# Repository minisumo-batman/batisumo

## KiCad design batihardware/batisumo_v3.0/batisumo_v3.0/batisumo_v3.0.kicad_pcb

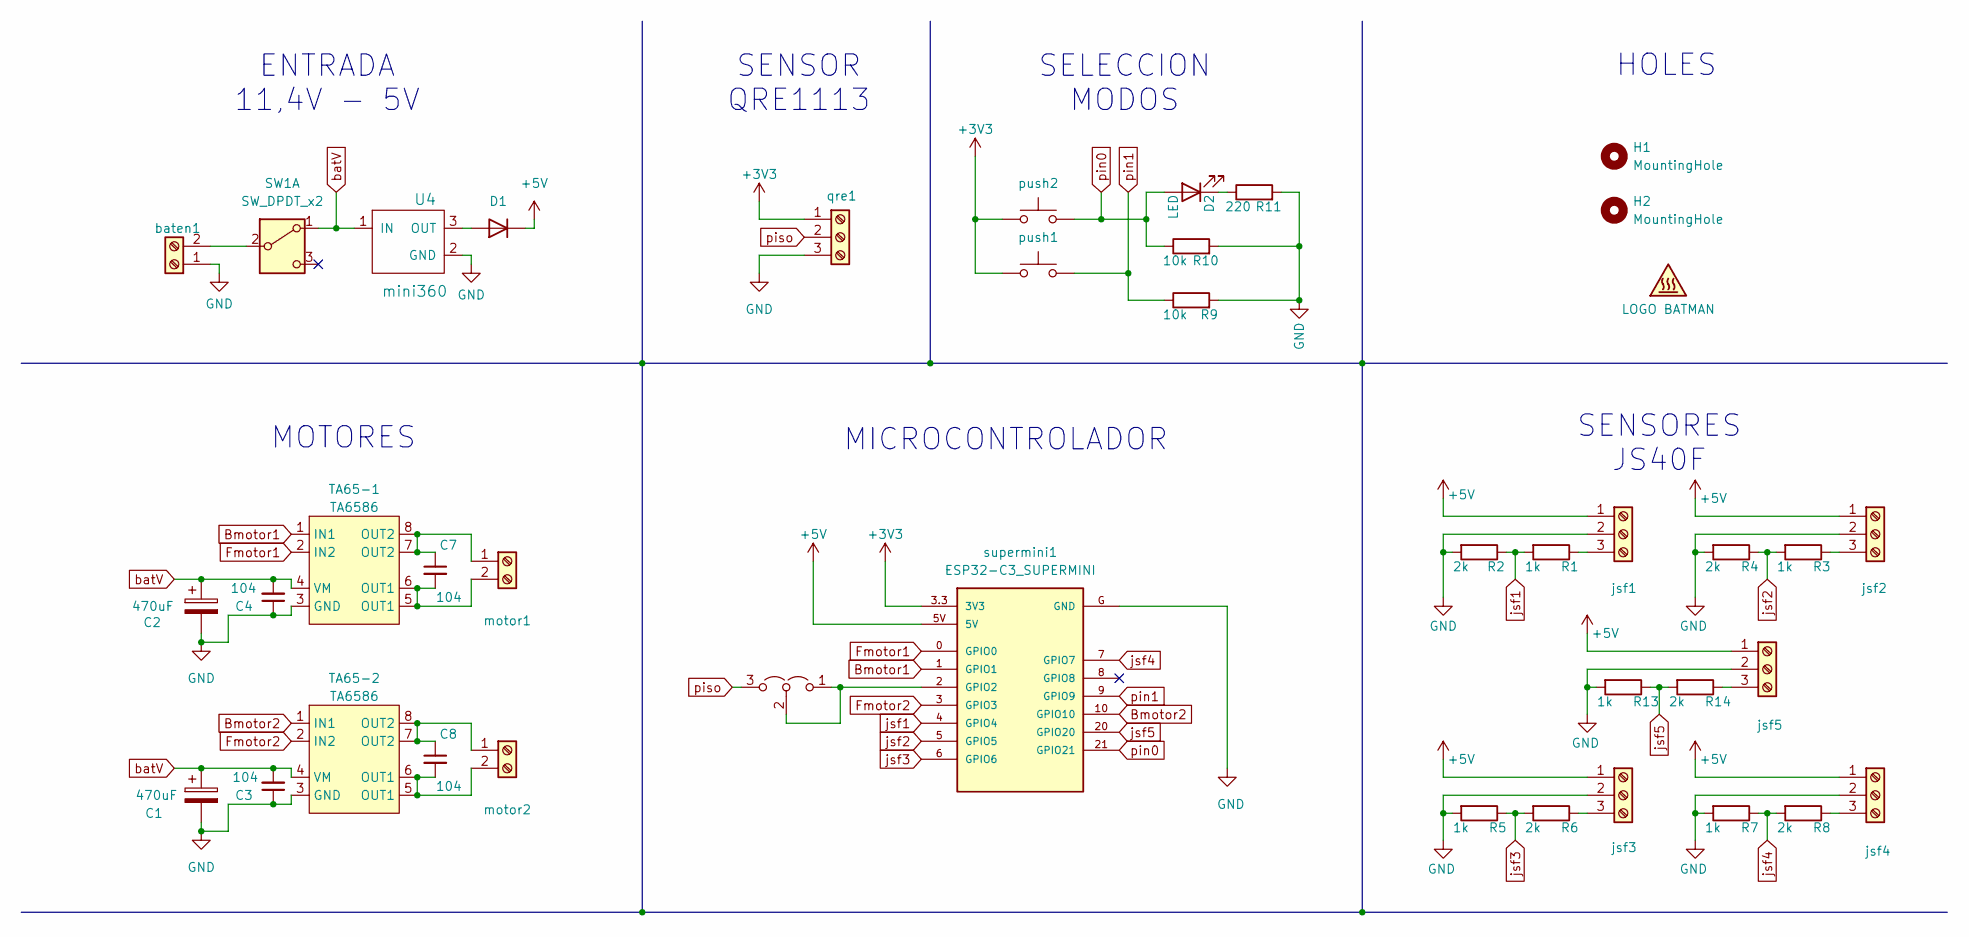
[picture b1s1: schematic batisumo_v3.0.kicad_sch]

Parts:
C1, C2: 470uF; CP_EIA-7343-43_Kemet-X
C3, C4, C7, C8: 104; C_0805_2012Metric
D1: D_2010_5025Metric_Pad1.52x2.65mm_HandSolder
D2: LED; LED_0805_2012Metric
H1, H2: MountingHole; MountingHole_3.2mm_M3
JP2: PinSocket_1x03_P2.54mm_Vertical
R1, R3, R5, R7, R13: 1k; R_0805_2012Metric
R2, R4, R6, R8, R14: 2k; R_0805_2012Metric
R9, R10: 10k; R_0805_2012Metric
R11: 220; R_0805_2012Metric
SW1: SW_DPDT_x2; SW_Slide-03_P2.54_L9_W4_H7
TA65-1, TA65-2: TA6586; DIP-8_W7.62mm
U4: mini360; Mini360_step-down
baten1: AMASS_XT30U-M_1x02_P5.0mm_Vertical
jsf1, jsf2, jsf3, jsf4, jsf5: JST_PH_B3B-PH-K_1x03_P2.00mm_Vertical
motor1, motor2: PinHeader_1x02_P2.54mm_Vertical
push1, push2: SW_Tactile_SPST_NO_Straight_CK_PTS636Sx25SMTRLFS
qre1: JST_PH_B3B-PH-K_1x03_P2.00mm_Vertical
supermini1: ESP32-C3_SUPERMINI; MODULE_ESP32-C3_SUPERMINI

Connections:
+3V3: push1.1, push2.1, qre1.1, supermini1.3.3 (3V3)
+5V: D1.1 (K), jsf1.1, jsf2.1, jsf3.1, jsf4.1, jsf5.1, supermini1.5V
Bmotor1: TA65-1.1 (IN1), supermini1.1 (GPIO1)
Bmotor2: TA65-2.1 (IN1), supermini1.10 (GPIO10)
Fmotor1: TA65-1.2 (IN2), supermini1.0 (GPIO0)
Fmotor2: TA65-2.2 (IN2), supermini1.3 (GPIO3)
GND: C1.2, C2.2, C3.1, C4.1, R2.2, R4.2, R5.2, R7.2, R9.2, R10.2, R11.2, R13.2, TA65-1.3 (GND), TA65-2.3 (GND), U4.2 (GND), baten1.1, jsf1.2, jsf2.2, jsf3.2, jsf4.2, jsf5.2, qre1.3, supermini1.G (GND)
unnamed: D1.2 (A), U4.3 (OUT)
unnamed: D2.1 (K), R11.1
unnamed: JP2.1 (A), JP2.2 (C), supermini1.2 (GPIO2)
unnamed: SW1.2 (B), baten1.2
unnamed: R1.1, jsf1.3
unnamed: R3.1, jsf2.3
unnamed: R6.1, jsf3.3
unnamed: R8.1, jsf4.3
unnamed: R14.1, jsf5.3
unnamed: C7.1, TA65-1.7 (OUT2), TA65-1.8 (OUT2), motor1.1
unnamed: C7.2, TA65-1.5 (OUT1), TA65-1.6 (OUT1), motor1.2
unnamed: C8.1, TA65-2.7 (OUT2), TA65-2.8 (OUT2), motor2.1
unnamed: C8.2, TA65-2.5 (OUT1), TA65-2.6 (OUT1), motor2.2
batV: C1.1, C2.1, C3.2, C4.2, SW1.1 (A), TA65-1.4 (VM), TA65-2.4 (VM), U4.1 (IN)
jsf1: R1.2, R2.1, supermini1.4 (GPIO4)
jsf2: R3.2, R4.1, supermini1.5 (GPIO5)
jsf3: R5.1, R6.2, supermini1.6 (GPIO6)
jsf4: R7.1, R8.2, supermini1.7 (GPIO7)
jsf5: R13.1, R14.2, supermini1.20 (GPIO20)
pin0: D2.2 (A), R10.1, push2.2, supermini1.21 (GPIO21)
pin1: R9.1, push1.2, supermini1.9 (GPIO9)
piso: JP2.3 (B), qre1.2

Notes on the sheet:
MOTORES
ENTRADA 11,4V - 5V
SENSOR QRE1113
SENSORES JS40F
HOLES
MICROCONTROLADOR
SELECCION MODOS

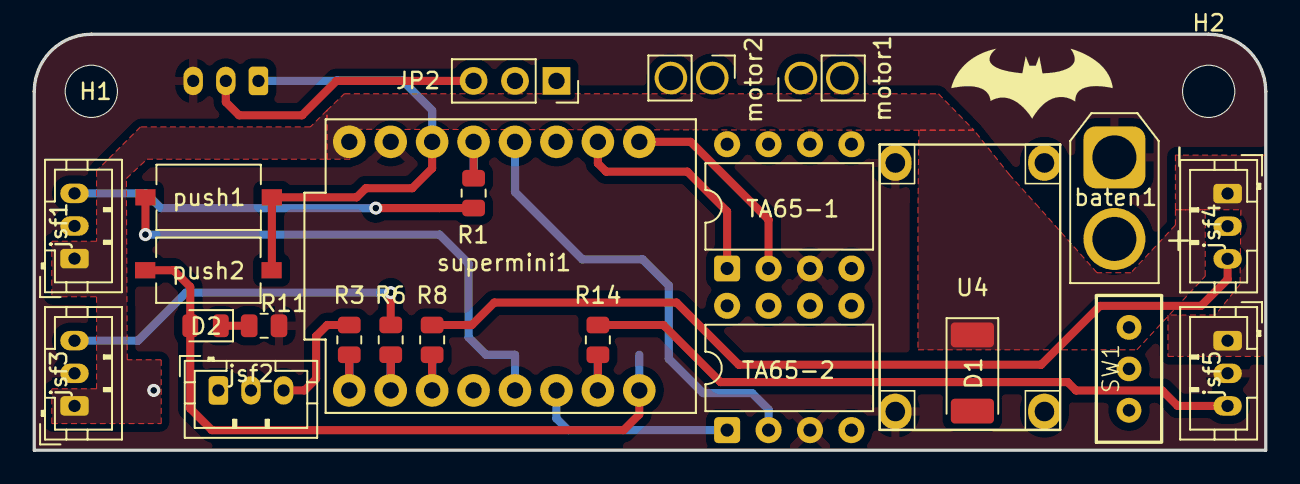
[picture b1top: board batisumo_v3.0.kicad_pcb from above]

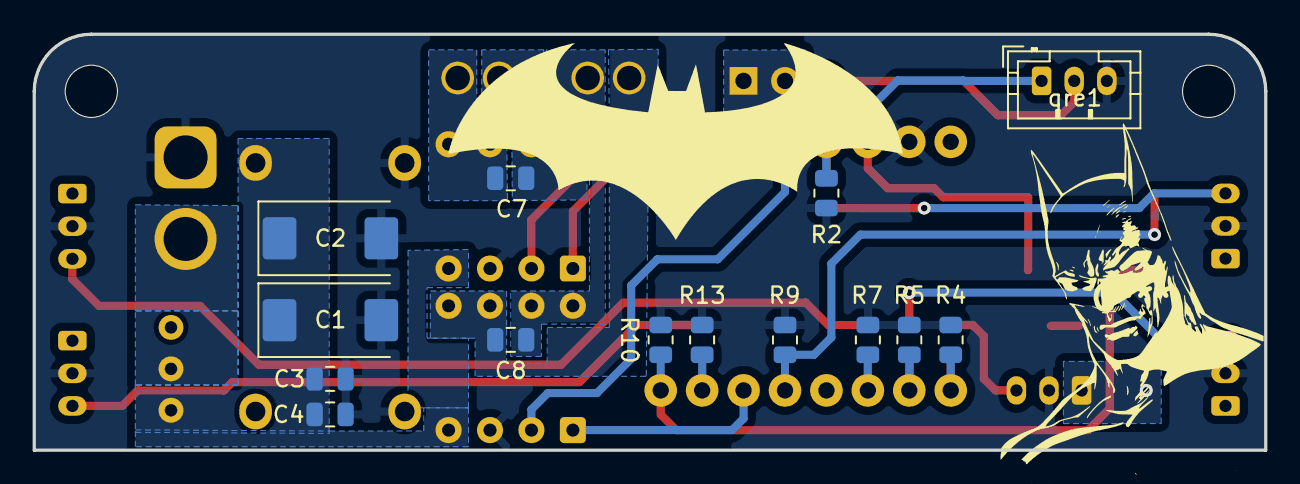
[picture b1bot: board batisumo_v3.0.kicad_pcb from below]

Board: 4 copper layers, 75.5 x 25.5 mm, 40 parts (14 on the bottom side), 29 nets.

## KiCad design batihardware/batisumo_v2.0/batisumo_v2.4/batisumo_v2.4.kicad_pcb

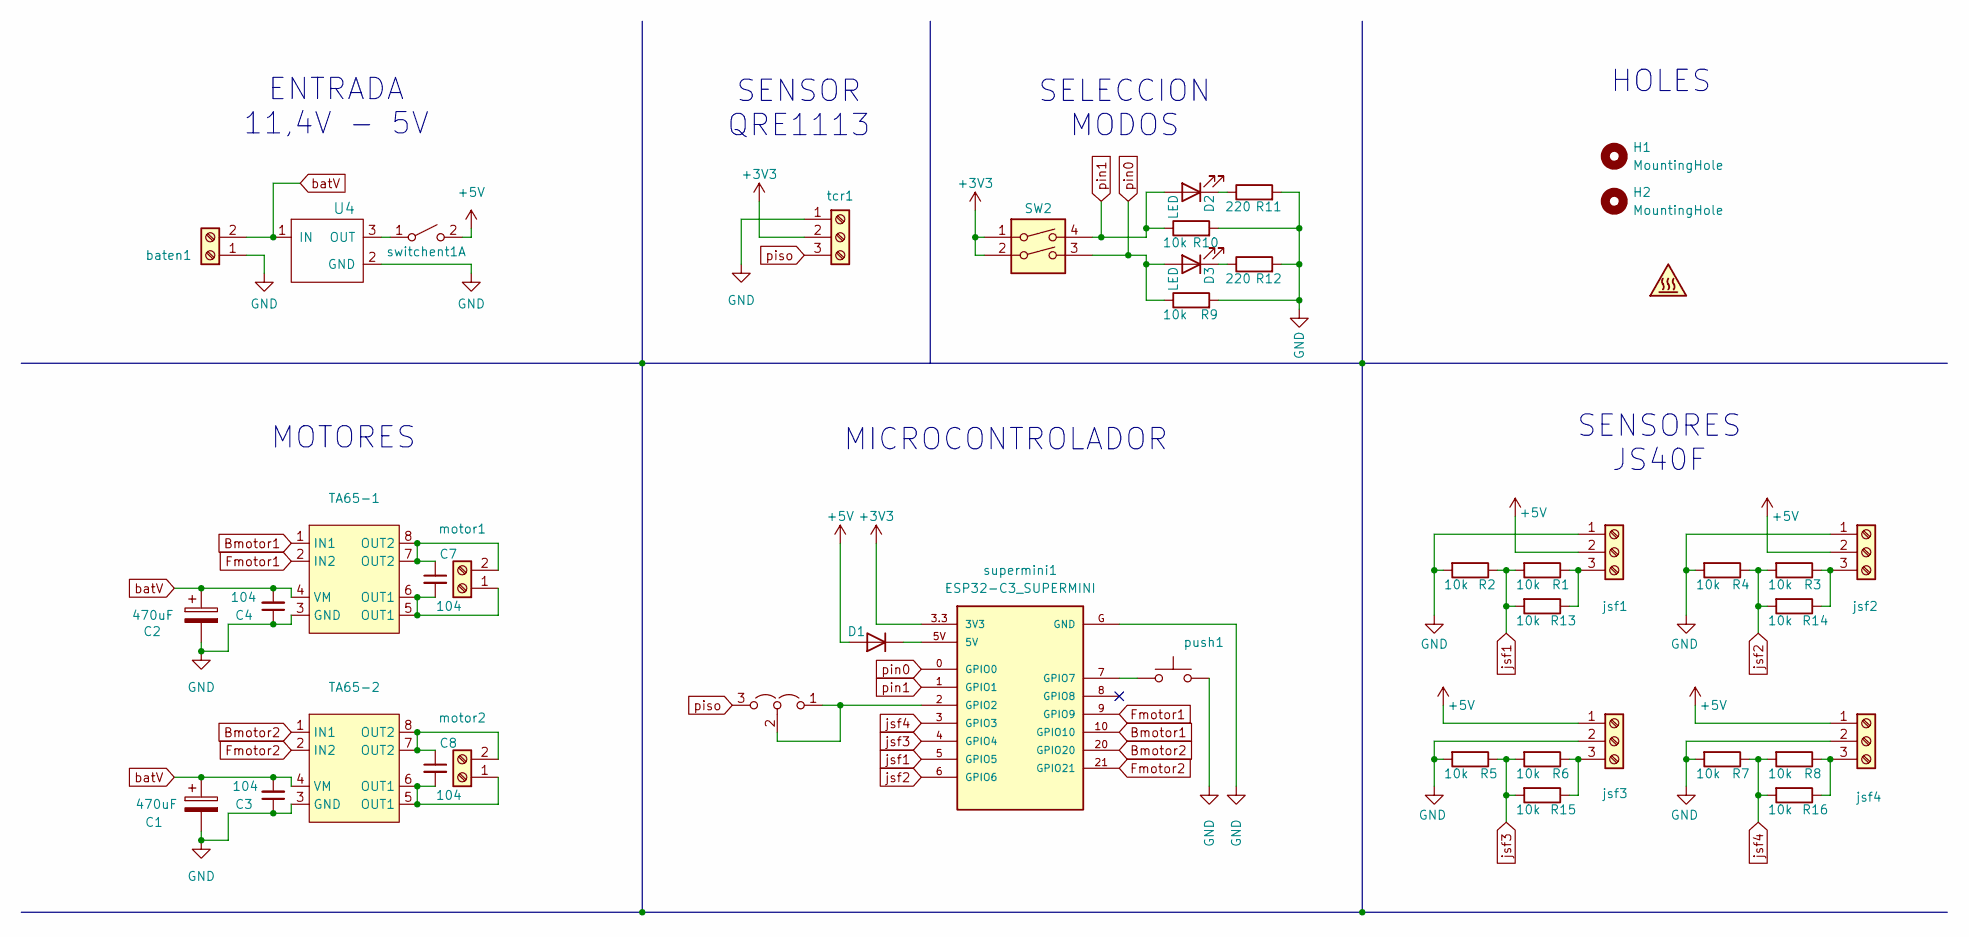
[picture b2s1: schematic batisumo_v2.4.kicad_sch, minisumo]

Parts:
C1, C2: 470uF; CP_Elec_10x10.5
C3, C4, C7, C8: 104; C_0805_2012Metric
D1: D_2010_5025Metric_Pad1.52x2.65mm_HandSolder
D2, D3: LED; LED_0805_2012Metric
H1, H2: MountingHole; MountingHole_3.2mm_M3
JP2: PinSocket_1x03_P2.54mm_Vertical
R1, R2, R3, R4, R5, R6, R7, R8, R9, R10, R13, R14, R15, R16: 10k; R_0805_2012Metric
R11, R12: 220; R_0805_2012Metric
SW2: SW_DIP_SPSTx02_Slide_9.78x7.26mm_W7.62mm_P2.54mm
TA65-1, TA65-2: DIP-8_W7.62mm
U4: Mini360_step-down
baten1: AMASS_XT30PW-M_1x02_P2.50mm_Horizontal
jsf1, jsf2, jsf3, jsf4: JST_PH_B3B-PH-K_1x03_P2.00mm_Vertical
motor1, motor2: TerminalBlock_TE_282834-2_1x02_P2.54mm_Horizontal
push1: SW_Tactile_SPST_NO_Straight_CK_PTS636Sx25SMTRLFS
supermini1: ESP32-C3_SUPERMINI; MODULE_ESP32-C3_SUPERMINI
switchent1: Molex_KK-254_AE-6410-02A_1x02_P2.54mm_Vertical
tcr1: JST_PH_B3B-PH-K_1x03_P2.00mm_Vertical

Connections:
+3V3: SW2.1, SW2.2, supermini1.3.3 (3V3), tcr1.2
+5V: D1.2 (A), jsf1.2, jsf2.2, jsf3.1, jsf4.1, switchent1.2 (B)
Bmotor1: TA65-1.1 (IN1), supermini1.10 (GPIO10)
Bmotor2: TA65-2.1 (IN1), supermini1.20 (GPIO20)
Fmotor1: TA65-1.2 (IN2), supermini1.9 (GPIO9)
Fmotor2: TA65-2.2 (IN2), supermini1.21 (GPIO21)
GND: C1.2, C2.2, C3.1, C4.1, R2.2, R4.2, R5.2, R7.2, R9.2, R10.2, R11.2, R12.2, TA65-1.3 (GND), TA65-2.3 (GND), U4.2 (GND), baten1.1, jsf1.1, jsf2.1, jsf3.2, jsf4.2, push1.2, supermini1.G (GND), tcr1.1
unnamed: D1.1 (K), supermini1.5V
unnamed: D2.1 (K), R11.1
unnamed: D3.1 (K), R12.1
unnamed: JP2.1 (A), JP2.2 (C), supermini1.2 (GPIO2)
unnamed: U4.3 (OUT), switchent1.1 (A)
unnamed: R1.1, R13.1, jsf1.3
unnamed: R3.1, R14.1, jsf2.3
unnamed: R6.1, R15.1, jsf3.3
unnamed: R8.1, R16.1, jsf4.3
unnamed: C7.2, TA65-1.5 (OUT1), TA65-1.6 (OUT1), motor1.1
unnamed: C7.1, TA65-1.7 (OUT2), TA65-1.8 (OUT2), motor1.2
unnamed: C8.2, TA65-2.5 (OUT1), TA65-2.6 (OUT1), motor2.1
unnamed: C8.1, TA65-2.7 (OUT2), TA65-2.8 (OUT2), motor2.2
unnamed: push1.1, supermini1.7 (GPIO7)
batV: C1.1, C2.1, C3.2, C4.2, TA65-1.4 (VM), TA65-2.4 (VM), U4.1 (IN), baten1.2
jsf1: R1.2, R2.1, R13.2, supermini1.5 (GPIO5)
jsf2: R3.2, R4.1, R14.2, supermini1.6 (GPIO6)
jsf3: R5.1, R6.2, R15.2, supermini1.4 (GPIO4)
jsf4: R7.1, R8.2, R16.2, supermini1.3 (GPIO3)
pin0: D3.2 (A), R9.1, SW2.3, supermini1.0 (GPIO0)
pin1: D2.2 (A), R10.1, SW2.4, supermini1.1 (GPIO1)
piso: JP2.3 (B), tcr1.3

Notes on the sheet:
SENSOR QRE1113
SELECCION MODOS
HOLES
MICROCONTROLADOR
ENTRADA 11,4V - 5V
MOTORES
SENSORES JS40F

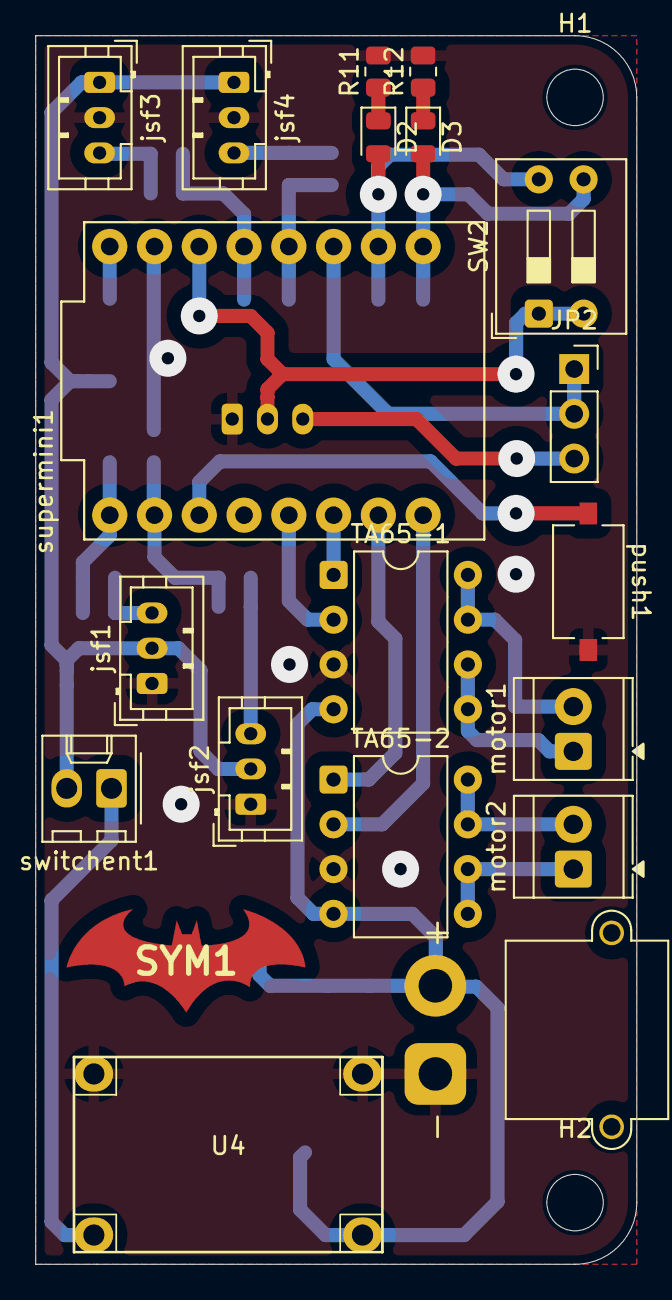
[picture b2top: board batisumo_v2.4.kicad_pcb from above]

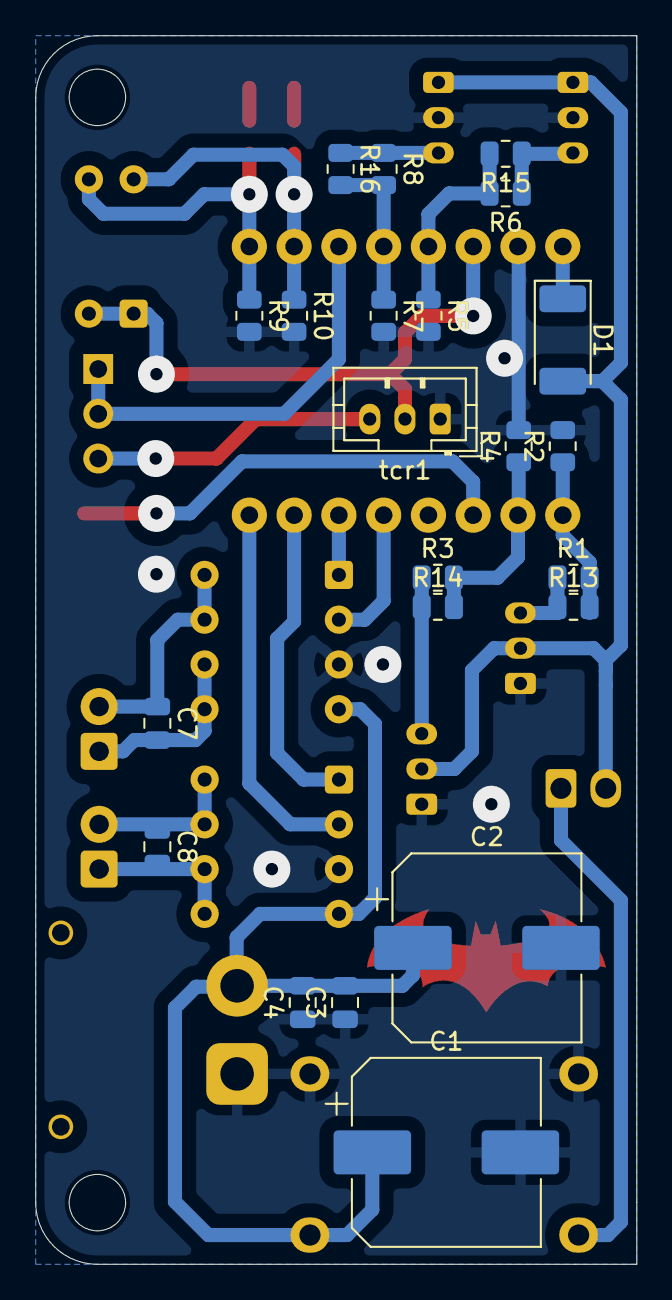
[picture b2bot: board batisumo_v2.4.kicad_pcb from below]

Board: 2 copper layers, 34.1 x 69.7 mm, 44 parts (22 on the bottom side), 29 nets.

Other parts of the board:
SYM1: SYM_EasterEgg_42x60mm; logo batman minisumo

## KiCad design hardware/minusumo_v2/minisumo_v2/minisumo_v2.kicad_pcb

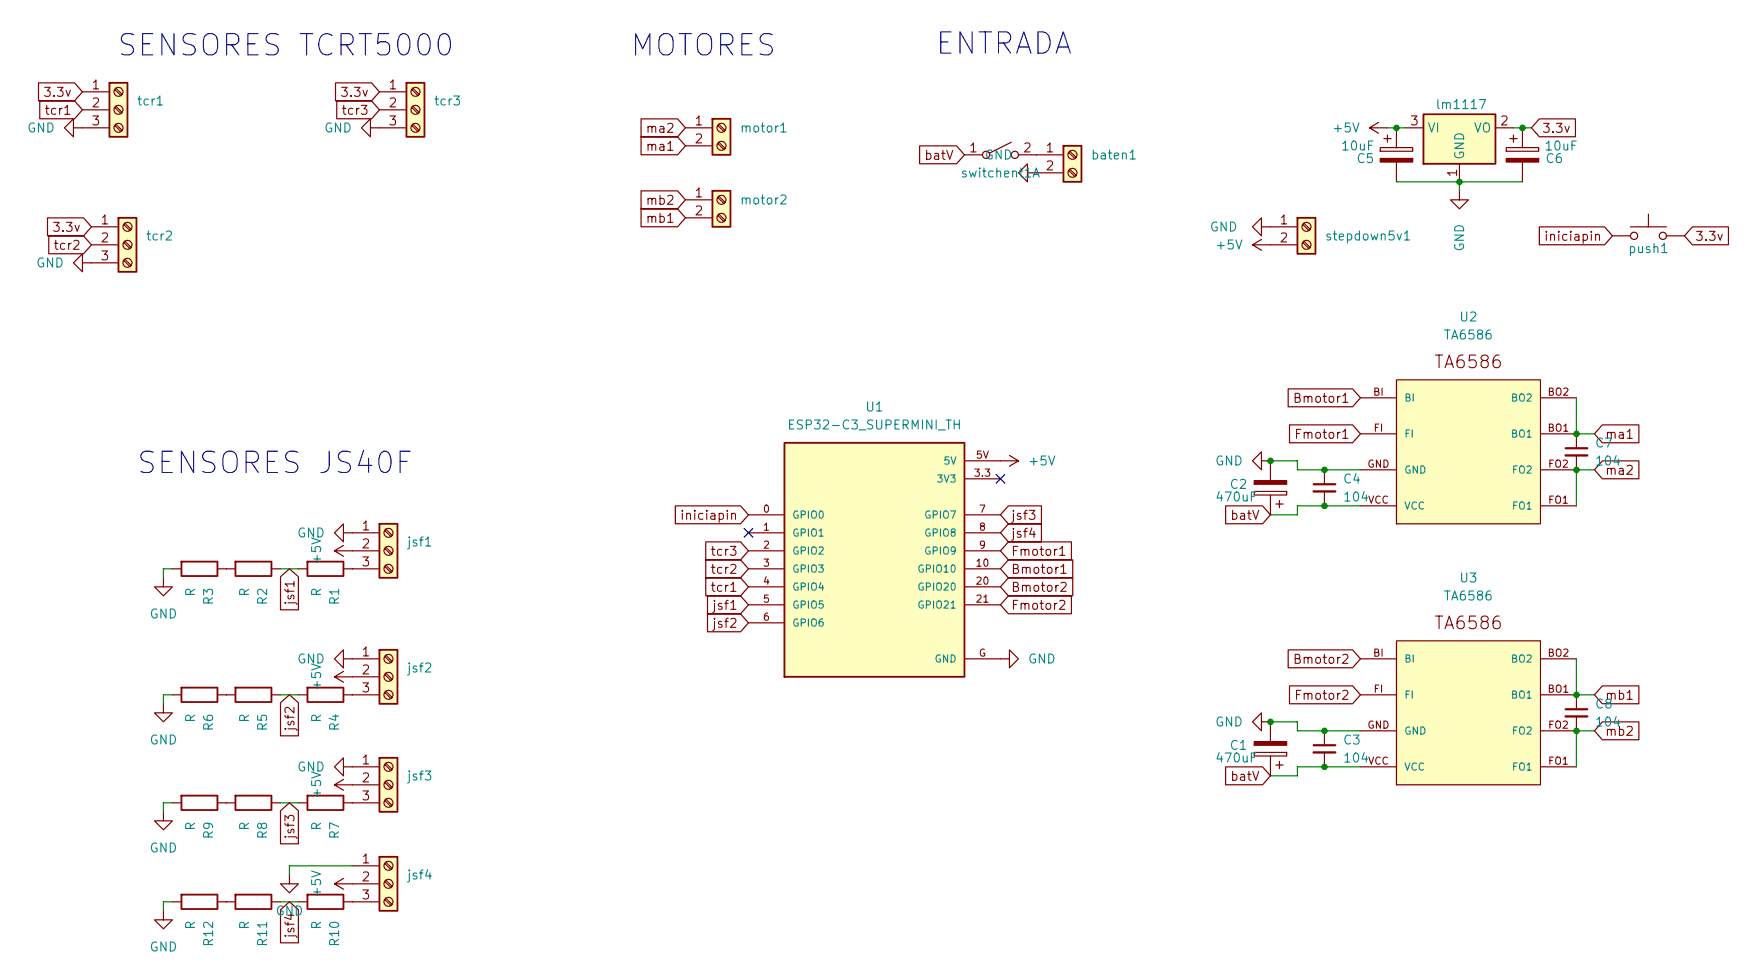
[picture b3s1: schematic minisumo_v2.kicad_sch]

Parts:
C1, C2: 470uF; CP_Elec_6.3x7.7
C3, C4, C7, C8: 104; C_0805_2012Metric
C5, C6: 10uF; C_0805_2012Metric
R1, R2, R3, R4, R5, R6, R7, R8, R9, R10, R11, R12: R; R_0805_2012Metric
U1: ESP32-C3_SUPERMINI_TH; MODULE_ESP32-C3_SUPERMINI
U2, U3: TA6586; TA6586-FOOTPRINT
baten1: Screw_Terminal_01x02; AMASS_XT30PW-M_1x02_P2.50mm_Horizontal
jsf1, jsf2, jsf3, jsf4: Screw_Terminal_01x03; JST_PH_B3B-PH-K_1x03_P2.00mm_Vertical
lm1117: LM1117MP-3.3; SOT-223-3_TabPin2
motor1, motor2: Screw_Terminal_01x02; TerminalBlock_TE_282834-2_1x02_P2.54mm_Horizontal
push1: SW_Push; Pulsador_SMD_2_ALTO
stepdown5v1: Screw_Terminal_01x02; TerminalBlock_TE_282834-2_1x02_P2.54mm_Horizontal
switchent1: SW_DPST_x2; Molex_KK-254_AE-6410-02A_1x02_P2.54mm_Vertical
tcr1, tcr2, tcr3: Screw_Terminal_01x03; JST_PH_B3B-PH-K_1x03_P2.00mm_Vertical

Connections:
3.3v: C6.1, lm1117.2 (VO), push1.2, tcr1.1, tcr2.1, tcr3.1
+5V: C5.1, U1.5V, jsf1.2, jsf2.2, jsf3.2, jsf4.2, lm1117.3 (VI), stepdown5v1.2
Bmotor1: U1.10 (GPIO10), U2.BI
Bmotor2: U1.20 (GPIO20), U3.BI
Fmotor1: U1.9 (GPIO9), U2.FI
Fmotor2: U1.21 (GPIO21), U3.FI
GND: C1.2, C2.2, C3.1, C4.1, C5.2, C6.2, R3.2, R6.2, R9.2, R12.2, U1.G (GND), U2.GND, U3.GND, baten1.2, jsf1.1, jsf2.1, jsf3.1, jsf4.1, lm1117.1 (GND), stepdown5v1.1, tcr1.3, tcr2.3, tcr3.3
unnamed: R2.2, R3.1
unnamed: R5.2, R6.1
unnamed: R8.2, R9.1
unnamed: R11.2, R12.1
unnamed: baten1.1, switchent1.2 (B)
unnamed: R1.1, jsf1.3
unnamed: R4.1, jsf2.3
unnamed: R7.1, jsf3.3
unnamed: R10.1, jsf4.3
batV: C1.1, C2.1, C3.2, C4.2, U2.VCC, U3.VCC, switchent1.1 (A)
iniciapin: U1.0 (GPIO0), push1.1
jsf1: R1.2, R2.1, U1.5 (GPIO5)
jsf2: R4.2, R5.1, U1.6 (GPIO6)
jsf3: R7.2, R8.1, U1.7 (GPIO7)
jsf4: R10.2, R11.1, U1.8 (GPIO8)
ma1: C7.1, U2.BO1, U2.BO2, motor1.2
ma2: C7.2, U2.FO1, U2.FO2, motor1.1
mb1: C8.1, U3.BO1, U3.BO2, motor2.2
mb2: C8.2, U3.FO1, U3.FO2, motor2.1
tcr1: U1.4 (GPIO4), tcr1.2
tcr2: U1.3 (GPIO3), tcr2.2
tcr3: U1.2 (GPIO2), tcr3.2

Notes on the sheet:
SENSORES TCRT5000
ENTRADA
MOTORES
SENSORES JS40F

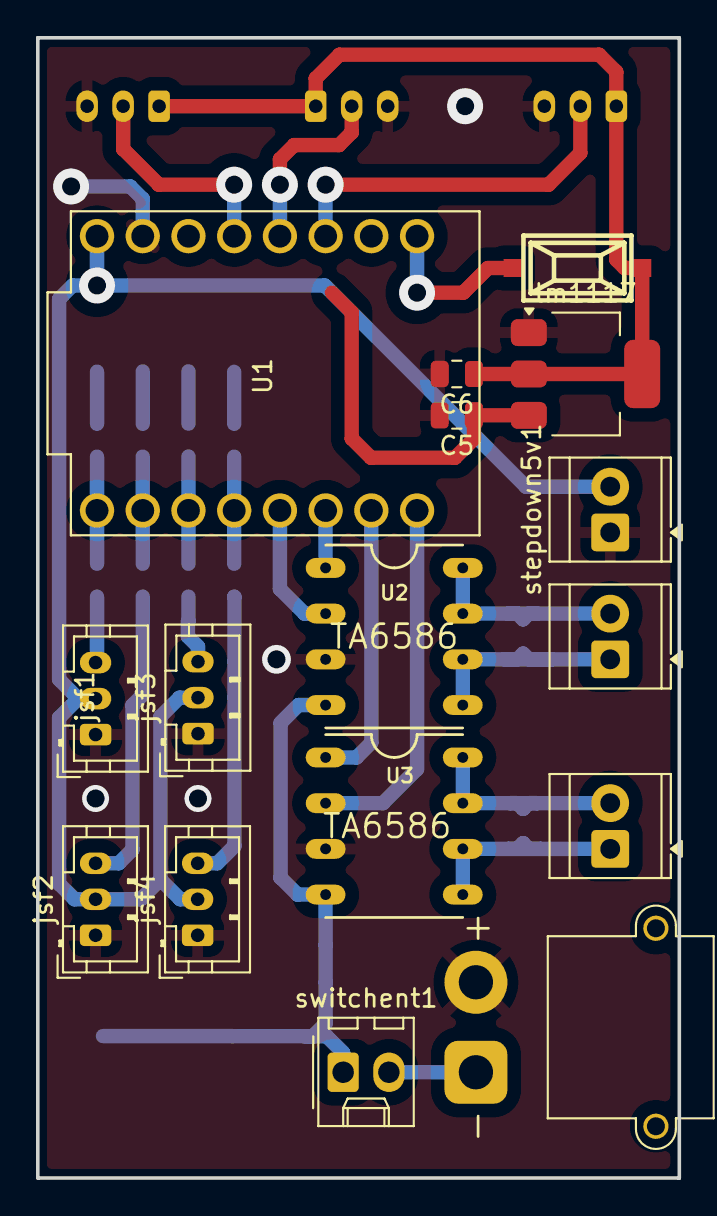
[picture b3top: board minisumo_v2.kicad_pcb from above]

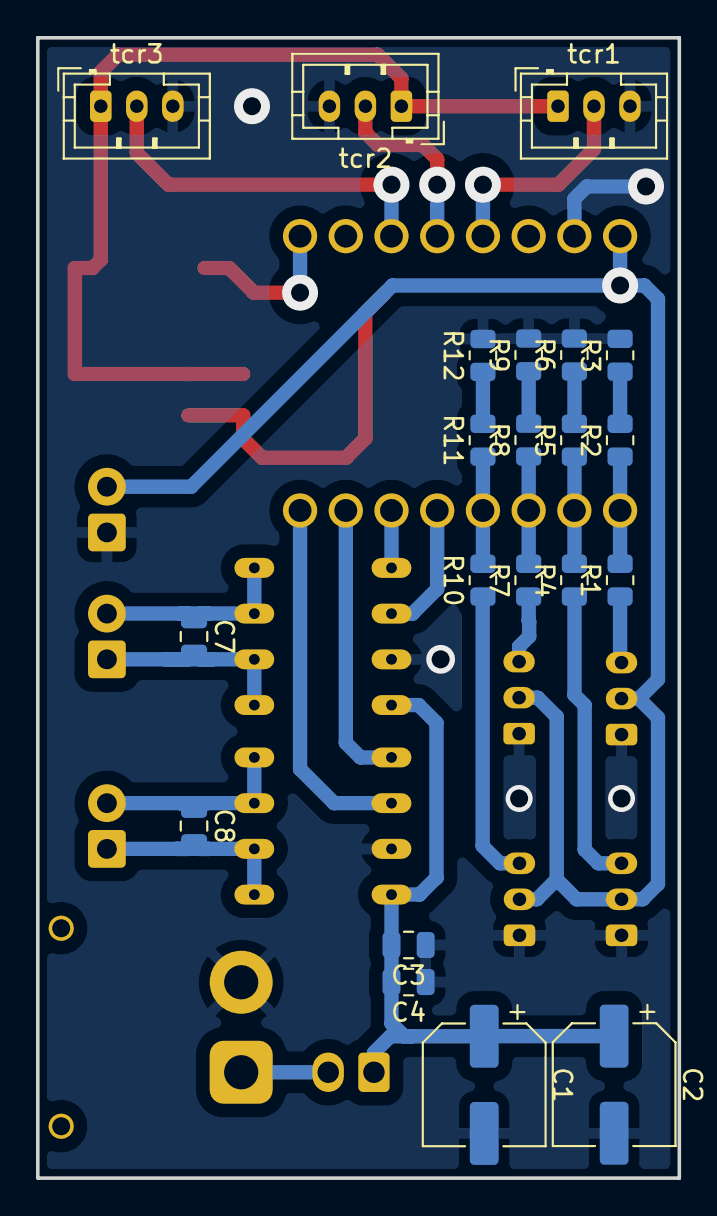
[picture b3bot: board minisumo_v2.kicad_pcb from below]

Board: 2 copper layers, 35.6 x 63.4 mm, 37 parts (21 on the bottom side), 29 nets.

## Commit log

2025-04-10 hardware batisumo
2025-04-10 Rename minisumo.kicad_pcb to Hardware/minisumo.kicad_pcb
2025-04-10 Rename minisumo.kicad_prl to Hardware/minisumo.kicad_prl
2025-04-10 Rename minisumo.kicad_pro to Hardware/minisumo.kicad_pro
2025-04-10 Rename minisumo.kicad_sch to Hardware/minisumo.kicad_sch
2025-04-14 commit version placa casi terminada
2025-06-07 v1.1
